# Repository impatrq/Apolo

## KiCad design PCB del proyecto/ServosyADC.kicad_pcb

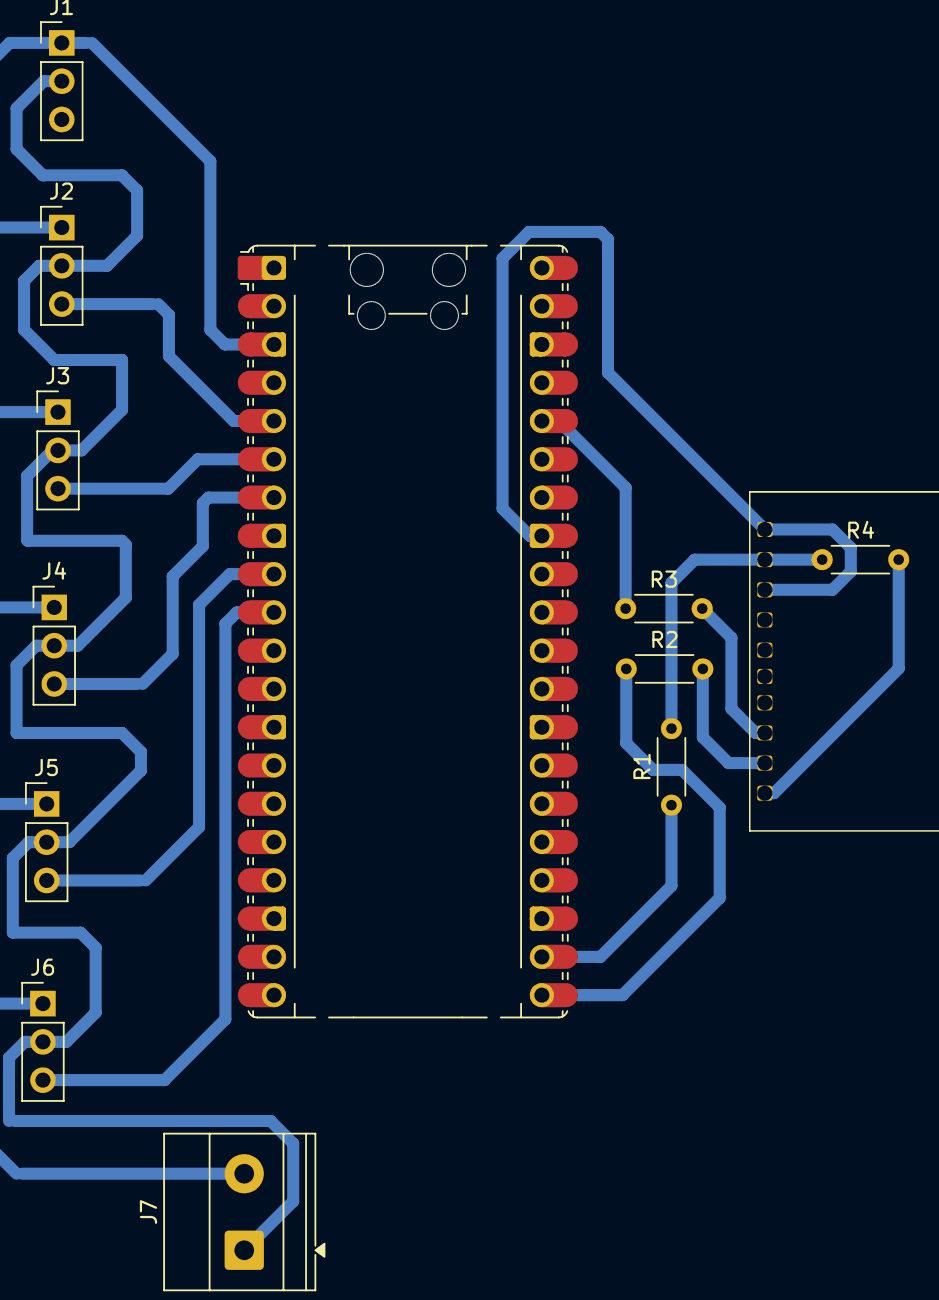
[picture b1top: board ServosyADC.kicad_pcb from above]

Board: 2 copper layers, 13 parts (0 on the bottom side), 16 nets.

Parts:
A1: RaspberryPi_Pico; RaspberryPi_Pico_Common_Unspecified
J1, J2, J3, J4, J5, J6: Conn_01x03_Pin; PinHeader_1x03_P2.54mm_Vertical
J7: Screw_Terminal_01x02; TerminalBlock_Phoenix_MKDS-1,5-2-5.08_1x02_P5.08mm_Horizont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
R1, R2, R3, R4: R; R_Axial_DIN0204_L3.6mm_D1.6mm_P5.08mm_Horizontal
U1: ADS1115IDGS; ADS

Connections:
+3.3V: A1.36 (3V3), R3.1
GND: A1.3 (GND), A1.8 (GND), A1.13 (GND), A1.18 (GND), A1.23 (GND), A1.28 (GND), A1.38 (GND), J1.1, J2.1, J3.1, J4.1, J5.1, J6.1, J7.2
unnamed: A1.33 (AGND), U1.1 (ADDR), U1.3 (GND)
unnamed: A1.4 (GPIO2), J1.3
unnamed: A1.5 (GPIO3), J2.3
unnamed: A1.6 (GPIO4), J3.3
unnamed: A1.7 (GPIO5), J4.3
unnamed: A1.9 (GPIO6), J5.3
unnamed: A1.10 (GPIO7), J6.3
unnamed: A1.21 (GPIO16), R2.1
unnamed: A1.22 (GPIO17), R1.1
unnamed: J1.2, J2.2, J3.2, J4.2, J5.2, J6.2, J7.1
unnamed: R1.2, R4.1, U1.2 (ALERT/RDY)
unnamed: R4.2, U1.10 (SCL)
unnamed: R2.2, U1.9 (SDA)
unnamed: R3.2, U1.8 (VDD)

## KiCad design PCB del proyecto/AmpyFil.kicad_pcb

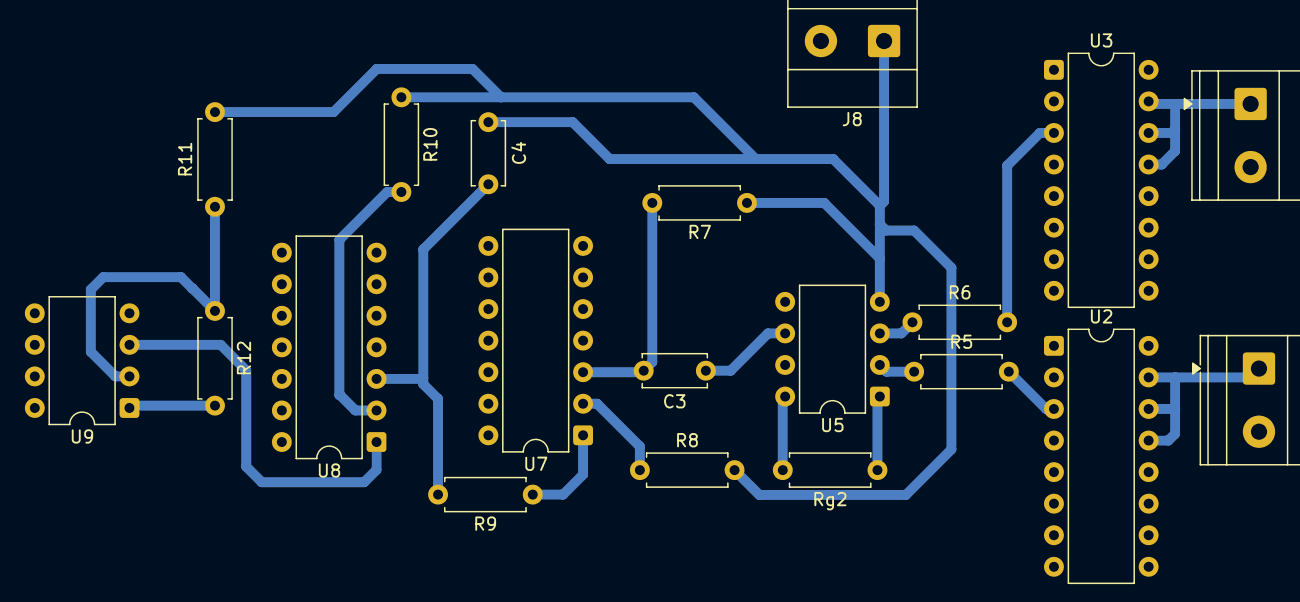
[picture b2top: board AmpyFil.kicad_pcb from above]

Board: 2 copper layers, 20 parts (0 on the bottom side), 18 nets.

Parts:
C3: 1µF; C_Disc_D5.0mm_W2.5mm_P5.00mm
C4: 100nF; C_Disc_D5.0mm_W2.5mm_P5.00mm
J8, J9, J10: Screw_Terminal_01x02; TerminalBlock_Phoenix_MKDS-1,5-2-5.08_1x02_P5.08mm_Horizont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
R5, R6: R; R_Axial_DIN0207_L6.3mm_D2.5mm_P7.62mm_Horizontal
R7: 8,2K; R_Axial_DIN0207_L6.3mm_D2.5mm_P7.62mm_Horizontal
R8, R10, R11: 10K; R_Axial_DIN0207_L6.3mm_D2.5mm_P7.62mm_Horizontal
R9: 3,3K; R_Axial_DIN0207_L6.3mm_D2.5mm_P7.62mm_Horizontal
R12: 90k; R_Axial_DIN0207_L6.3mm_D2.5mm_P7.62mm_Horizontal
Rg2: 500; R_Axial_DIN0207_L6.3mm_D2.5mm_P7.62mm_Horizontal
U2, U3: 74HC4051; DIP-16_W7.62mm
U5: AD620; DIP-8_W7.62mm
U7, U8: TL084; DIP-14_W7.62mm
U9: LM358; DIP-8_W7.62mm

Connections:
Electrodo +: R6.1, U5.3 (+)
Electrodo -: R5.1, U5.2 (-)
unnamed: C3.1, U5.6
unnamed: C4.1, J8.1 (Pin_1_1), R7.1, R8.2, R10.1, R11.2, U5.4 (Vs-)
unnamed: J9.1 (Pin_1_1), U2.13 (A0), U2.14 (A1), U2.15 (A2)
unnamed: J10.1 (Pin_1_1), U3.13 (A0), U3.14 (A1), U3.15 (A2)
unnamed: R9.1, U7.1
unnamed: Rg2.1, U5.1 (Rg)
unnamed: Rg2.2, U5.8 (Rg)
unnamed: R5.2, U2.3 (A)
unnamed: R6.2, U3.3 (A)
unnamed: C3.2, R7.2, U7.3 (+)
unnamed: R8.1, U7.2 (-)
unnamed: C4.2, R9.2, U8.3 (+)
unnamed: R10.2, U8.2 (-)
unnamed: U8.1, U9.3 (+)
unnamed: R11.1, R12.1, U9.2 (-)
Salida AMP: R12.2, U9.1

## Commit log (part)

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2026-04-15 Agrego Codigo-Apolo
2026-04-15 Delete Apolo directory
    sadsaf
2026-04-29 Reorganize project folders
2026-04-29 Remove .vscode folder
2026-04-29 Move PDF to Documentos folder
2026-04-29 Add gitignore
2026-04-29 Remove root build folder
2026-04-29 Stop tracking build and vscode
2026-04-30 Actualizar codigo de control EMG y servos
2026-06-09 docs: actualizar documentación del proyecto
2026-06-09 Remove build and vscode files
2026-06-24 Backup del codigo funcionando
